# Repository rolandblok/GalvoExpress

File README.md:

# GalvoExpress
Driver and electronics to drive A-express galvo with mircrocontroller

## Kicad
V1.1 : 
- fix transistor for laser : this was wrong
- DAC was completely wrong

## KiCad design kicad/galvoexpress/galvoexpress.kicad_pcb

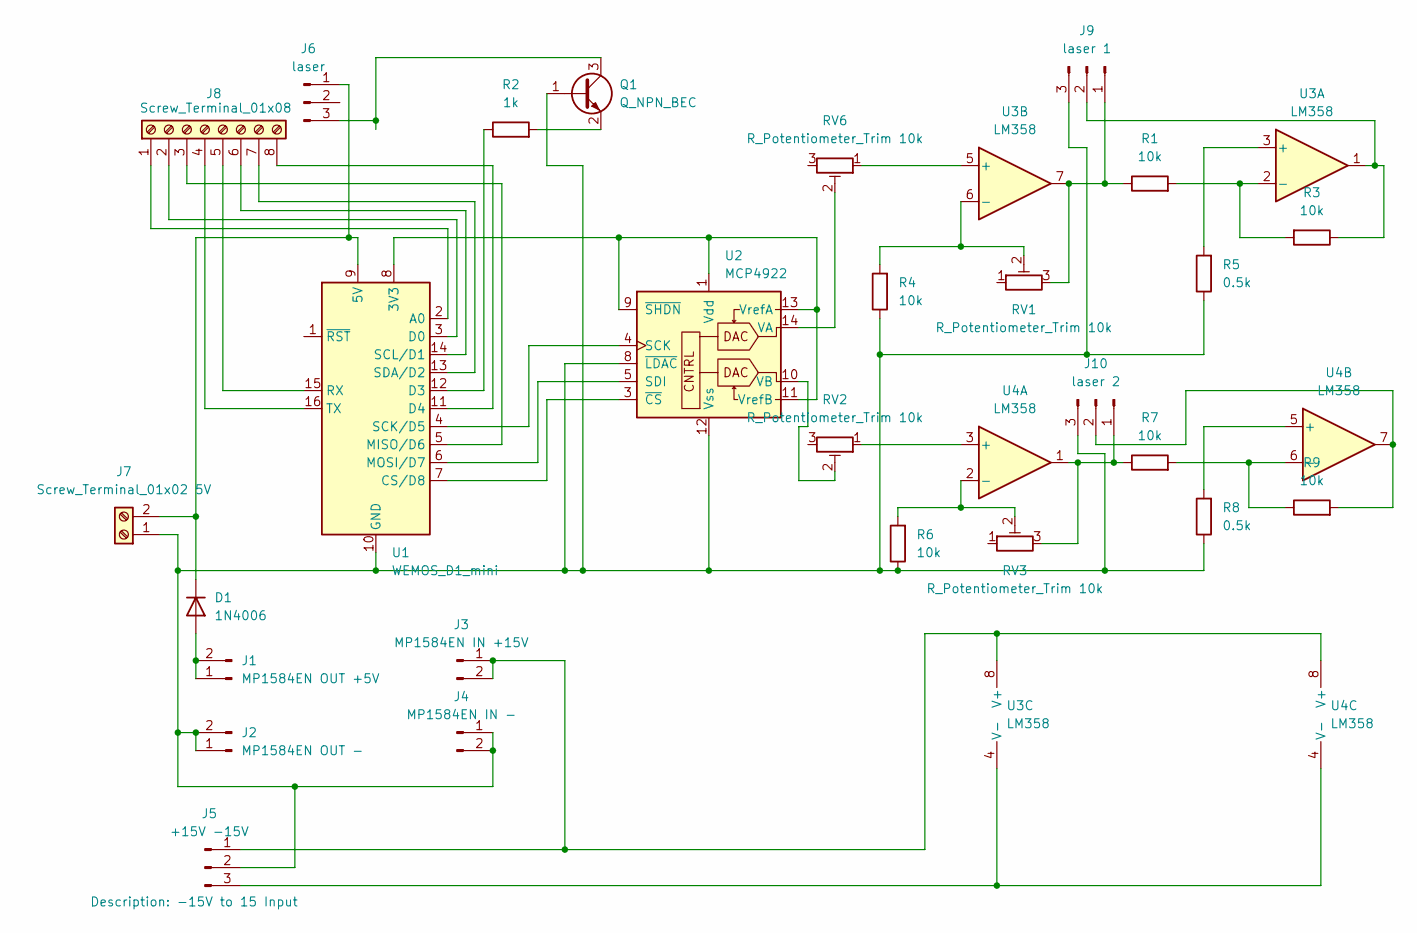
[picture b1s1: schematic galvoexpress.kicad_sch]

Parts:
D1: 1N4006; D_DO-41_SOD81_P10.16mm_Horizontal
J1: MP1584EN OUT +5V; PinHeader_1x02_P2.54mm_Vertical
J2: MP1584EN OUT -; PinHeader_1x02_P2.54mm_Vertical
J3: MP1584EN IN +15V; PinHeader_1x02_P2.54mm_Vertical
J4: MP1584EN IN -; PinHeader_1x02_P2.54mm_Vertical
J5: +15V -15V; JST_XH_S3B-XH-A-1_1x03_P2.50mm_Horizontal
J6: laser; PinHeader_1x03_P2.54mm_Vertical
J7: Screw_Terminal_01x02 5V; TerminalBlock_MetzConnect_Type059_RT06302HBWC_1x02_P3.50mm_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
J8: Screw_Terminal_01x08; TerminalBlock_Phoenix_MPT-0,5-8-2.54_1x08_P2.54mm_Horizontal
J9: laser 1; JST_XH_S3B-XH-A-1_1x03_P2.50mm_Horizontal
J10: laser 2; JST_XH_S3B-XH-A-1_1x03_P2.50mm_Horizontal
Q1: Q_NPN_BEC; TO-92L_Inline
R1, R3, R4, R6, R7, R9: 10k; R_Axial_DIN0309_L9.0mm_D3.2mm_P12.70mm_Horizontal
R2: 1k; R_Axial_DIN0309_L9.0mm_D3.2mm_P12.70mm_Horizontal
R5, R8: 0.5k; R_Axial_DIN0309_L9.0mm_D3.2mm_P12.70mm_Horizontal
RV1, RV2, RV3, RV6: R_Potentiometer_Trim 10k; Potentiometer_Bourns_3296W_Vertical
U1: WEMOS_D1_mini; WEMOS_D1_mini_light
U2: MCP4922; DIP-14_W7.62mm
U3, U4: LM358; DIP-8_W7.62mm

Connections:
unnamed: D1.2 (A), J1.1, J1.2
unnamed: D1.1 (K), J6.1, J7.2, U1.9 (5V)
unnamed: J3.1, J3.2, J5.1, U3.8 (V+), U4.8 (V+)
unnamed: J5.3, U3.4 (V-), U4.4 (V-)
unnamed: J6.3, Q1.3 (C)
unnamed: J8.1, U1.2 (A0)
unnamed: J8.2, U1.3 (D0)
unnamed: J8.3, U1.5 (MISO/D6)
unnamed: J8.4, U1.16 (TX)
unnamed: J8.5, U1.15 (RX)
unnamed: J8.6, U1.14 (SCL/D1)
unnamed: J8.7, U1.13 (SDA/D2)
unnamed: J8.8, U1.11 (D4)
unnamed: J9.1, R1.1, RV1.3, U3.7
unnamed: J9.2, R3.1, U3.1
unnamed: J10.1, R7.1, RV3.3, U4.1
unnamed: J10.2, R9.2, U4.7
unnamed: J2.1, J2.2, J4.1, J4.2, J5.2, J7.1, J9.3, J10.3, Q1.1 (B), R4.1, R5.1, R6.1, R8.1, U1.10 (GND), U2.8 (~LDAC), U2.12 (Vss)
unnamed: Q1.2 (E), R2.2
unnamed: U1.8 (3V3), U2.1 (Vdd), U2.9 (~SHDN), U2.11 (VrefB), U2.13 (VrefA)
unnamed: U1.7 (CS/D8), U2.3 (~CS)
unnamed: R2.1, U1.12 (D3)
unnamed: U1.6 (MOSI/D7), U2.5 (SDI)
unnamed: U1.4 (SCK/D5), U2.4 (SCK)
unnamed: RV6.2, U2.14 (VA)
unnamed: RV2.2, U2.10 (VB)
unnamed: R5.2, U3.3 (+)
unnamed: R1.2, R3.2, U3.2 (-)
unnamed: RV6.1, U3.5 (+)
unnamed: R4.2, RV1.2, U3.6 (-)
unnamed: RV2.1, U4.3 (+)
unnamed: R6.2, RV3.2, U4.2 (-)
unnamed: R8.2, U4.5 (+)
unnamed: R7.2, R9.1, U4.6 (-)

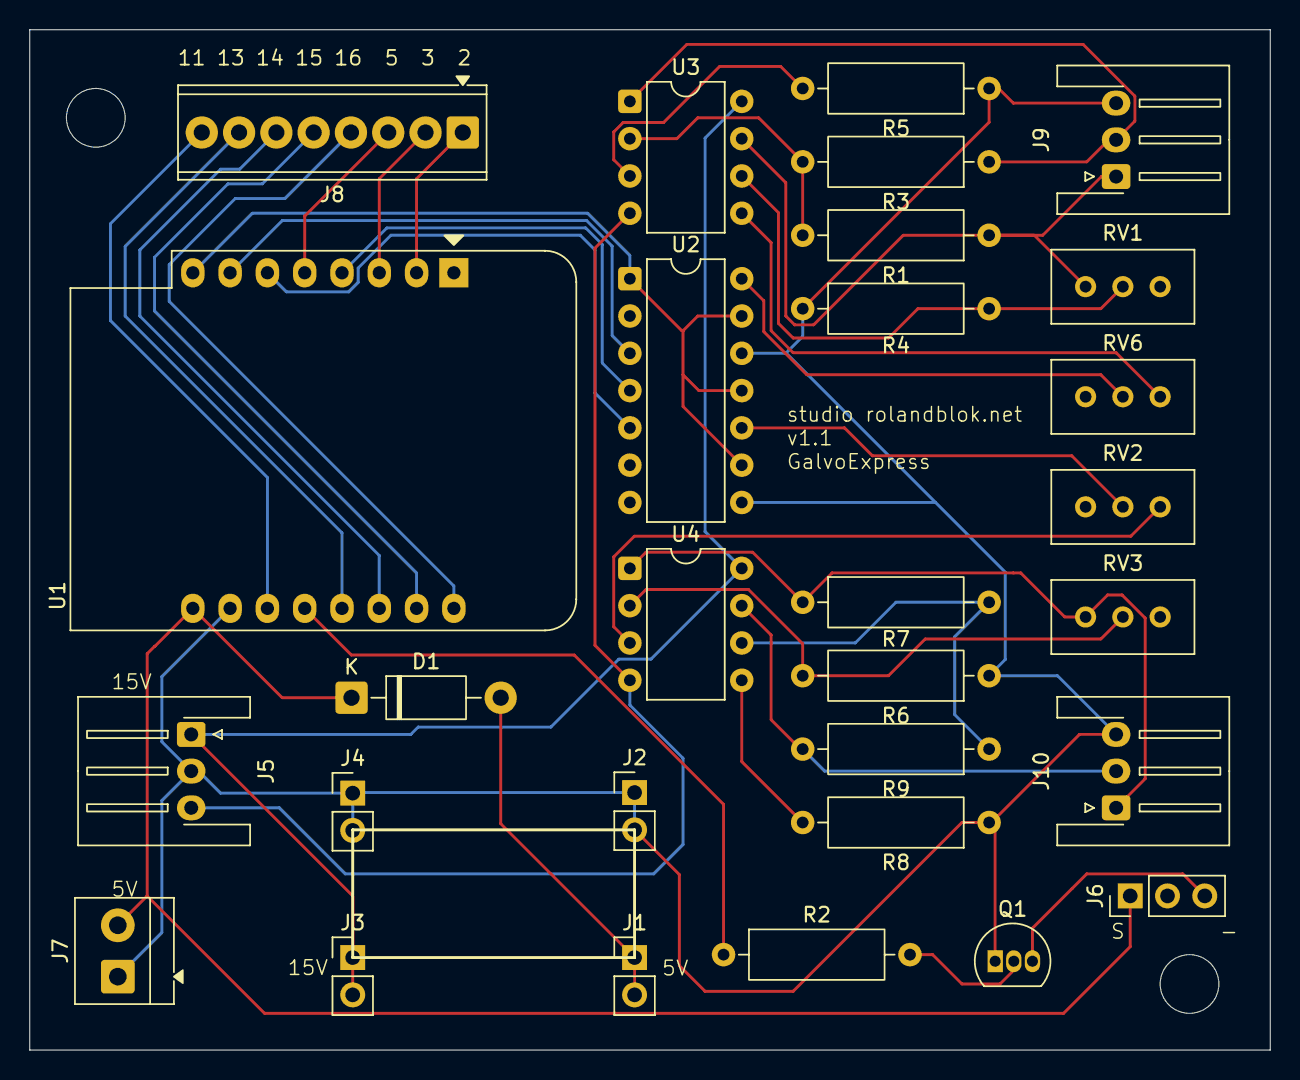
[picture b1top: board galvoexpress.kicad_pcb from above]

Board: 2 copper layers, 84.5 x 69.5 mm, 29 parts (0 on the bottom side), 34 nets.

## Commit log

2025-12-19 move the initial project to github
2025-12-19 first circle and square
2025-12-23 points and lines
2025-12-24 rude version SVG import
2025-12-24 added cubic bezier
2025-12-24 start on patern to arduino
2025-12-24 make uploadert
2025-12-24 somehow not better
2025-12-24 galvo uscontroller debugging
2025-12-24 wrukt met aircision enzo
2025-12-25 center and order
2025-12-30 new MCP4922
2026-01-04 start kicad
2026-01-04 hele schema
2026-01-04 start saving stuffs
2026-01-05 autosave should work
2026-01-05 small cleanrup
2026-01-06 delay for laser andor position
2026-01-16 kicad WIP
2026-01-23 kicad v1.0
2026-01-23 slowly better, cannot save full pattern yet
2026-02-06 memory optimize
2026-02-06 kicad repairs
2026-02-06 bug report PCB
